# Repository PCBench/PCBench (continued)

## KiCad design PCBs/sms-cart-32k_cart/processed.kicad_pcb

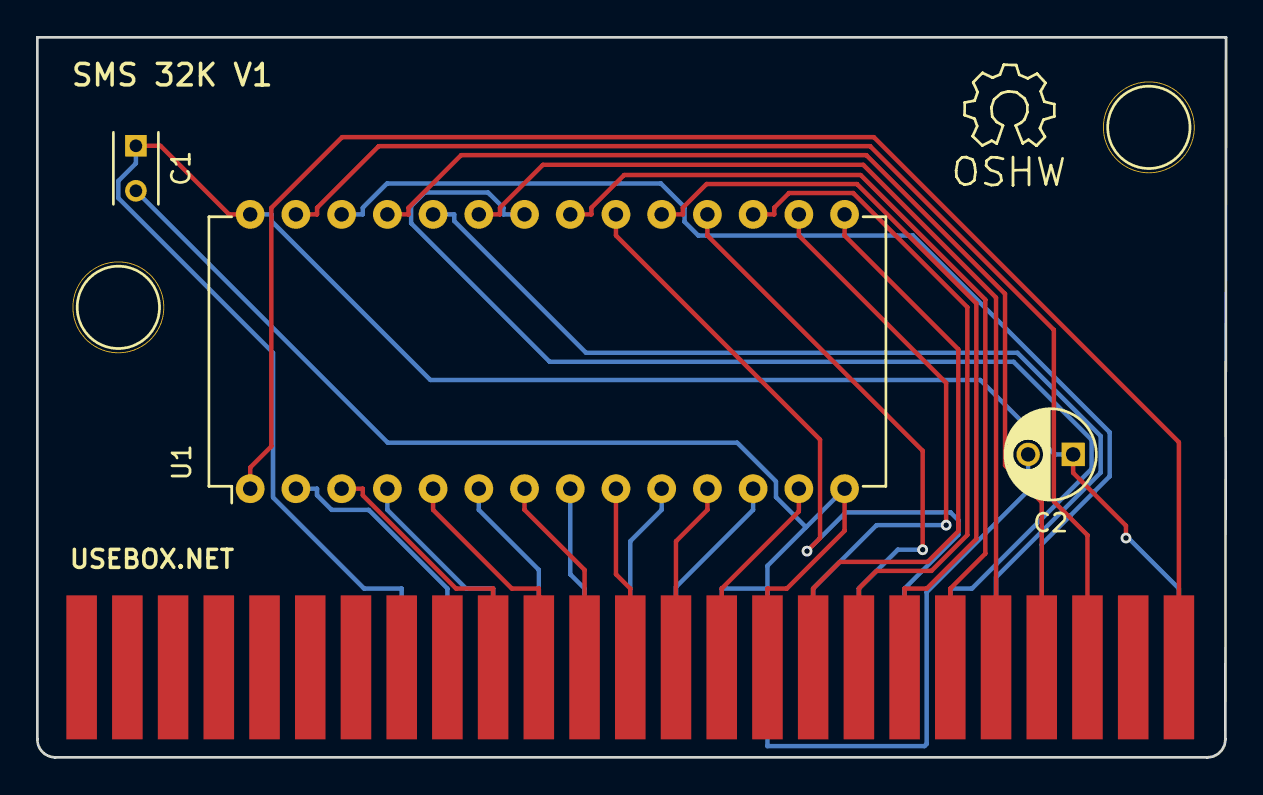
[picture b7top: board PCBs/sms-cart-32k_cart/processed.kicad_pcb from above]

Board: 2 copper layers, 66.0 x 40.0 mm, 7 parts (0 on the bottom side), 28 nets.

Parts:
C1: 100nF; C_Rect_L4_W2.5_P2.5
C2: 4.7uF; C_Radial_D5_L6_P2.5
OSHW1: Symbol_OSHW-Logo_SilkScreen
P1: CONN_SMS; CONN1
SCREW1, SCREW2: 1pin
U1: 27C256; DIP-28_W15.24mm

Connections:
/a0: P1.25, U1.10
/a1: P1.26, U1.9
/a2: P1.27, U1.8
/a3: P1.28, U1.7
/a4: P1.29, U1.6
/a5: P1.30, U1.5
/a6: P1.31, U1.4
/a7: P1.32, U1.3
/a8: P1.8, U1.25
/a9: P1.9, U1.24
/a10: P1.12, U1.21
/a11: P1.10, U1.23
/a12: P1.33, U1.2
/a13: P1.7, U1.26
/a14: P1.6, U1.27
/a15: P1.2, U1.1
/d0: P1.24, U1.11
/d1: P1.23, U1.12
/d2: P1.22, U1.13
/d3: P1.18, U1.15
/d4: P1.17, U1.16
/d5: P1.16, U1.17
/d6: P1.15, U1.18
/d7: P1.14, U1.19
CE: P1.13, U1.20
GND: C1.2, C2.2, P1.19, P1.20, P1.21, U1.14
OE: P1.11, U1.22
VCC: C1.1, C2.1, P1.1, P1.35, U1.28
